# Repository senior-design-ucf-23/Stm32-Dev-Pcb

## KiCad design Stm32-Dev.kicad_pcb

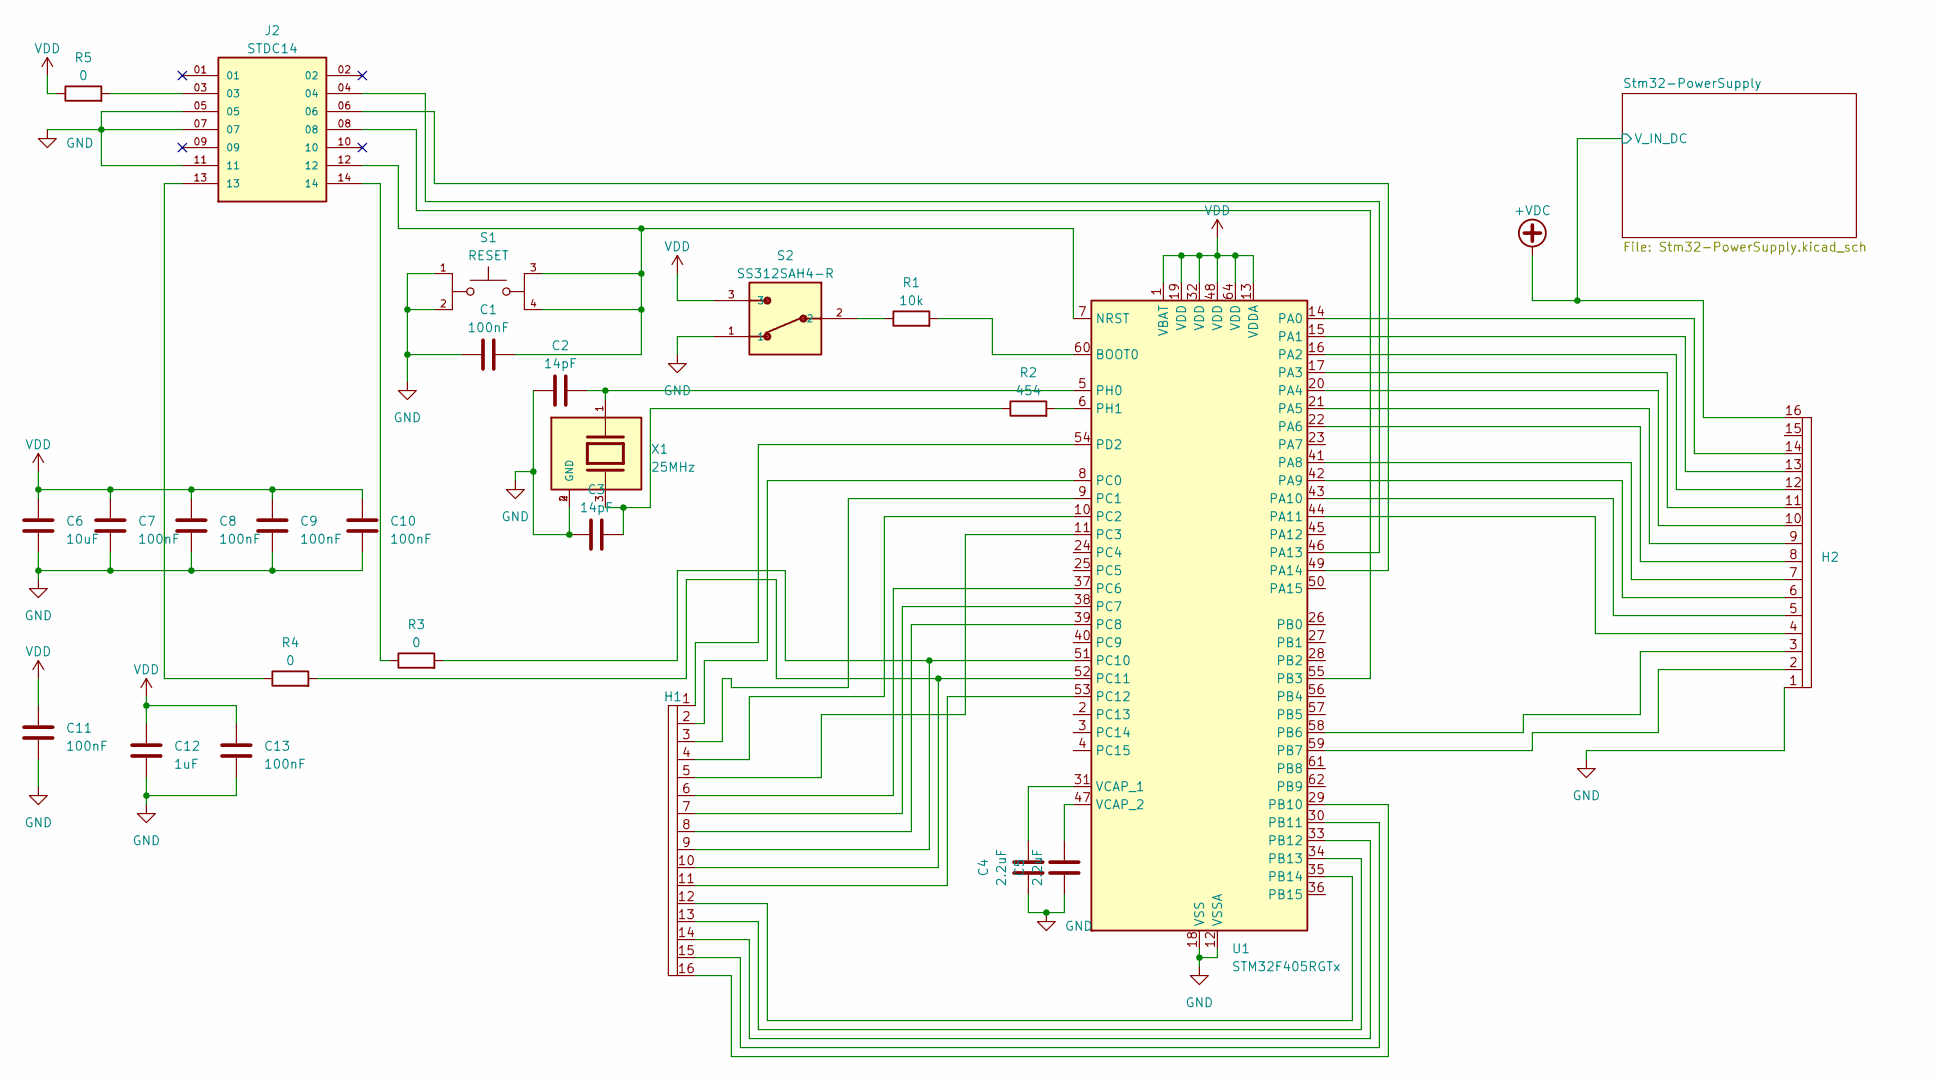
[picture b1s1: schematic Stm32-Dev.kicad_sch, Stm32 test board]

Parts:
C1, C7, C8, C9, C10, C11, C13: 100nF; C_0805_2012Metric
C2, C3: 14pF; C_0805_2012Metric
C4, C5: 2.2uF; C_0805_2012Metric
C6: 10uF; C_0805_2012Metric
C12: 1uF; C_0805_2012Metric
H1, H2: HDRV16
J2: STDC14; SAMTEC_FTSH-107-01-L-DV-K; PARTREV R
R1: 10k; R_0805_2012Metric
R2: 454; R_0805_2012Metric
R3, R4, R5: 0; R_0805_2012Metric
S1: RESET; SW_TL3301AF160QG; PARTREV E
S2: SS312SAH4-R; SW_SS312SAH4-R
U1: STM32F405RGTx; LQFP-64_10x10mm_P0.5mm
X1: 25MHz; XTAL_ABM10W-25.0000MHZ-7-D1X-T3; PARTREV 10.06.2020

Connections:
+VDC: H2.16; also elsewhere on the board
GND: C1.2, C2.2, C3.2, C4.2, C5.2, C6.2, C7.2, C8.2, C9.2, C10.2, C11.2, C12.2, C13.2, H2.1, J2.05, J2.07, J2.11, S1.1, S1.2, S2.1, U1.12 (VSSA), U1.18 (VSS), U1.63 (VSS), X1.2 (GND), X1.4 (GND); also elsewhere on the board
unnamed: C3.1, R2.1, X1.3
unnamed: J2.03, R5.2
unnamed: J2.13, R4.1
unnamed: J2.14, R3.1
unnamed: R1.1, S2.2
unnamed: R1.2, U1.60 (BOOT0)
unnamed: C1.1, J2.12, S1.3, S1.4, U1.7 (NRST)
unnamed: H2.14, U1.14 (PA0)
unnamed: H2.13, U1.15 (PA1)
unnamed: H2.12, U1.16 (PA2)
unnamed: H2.11, U1.17 (PA3)
unnamed: H2.10, U1.20 (PA4)
unnamed: H2.9, U1.21 (PA5)
unnamed: H2.8, U1.22 (PA6)
unnamed: H2.7, U1.41 (PA8)
unnamed: H2.6, U1.42 (PA9)
unnamed: H2.5, U1.43 (PA10)
unnamed: H2.4, U1.44 (PA11)
unnamed: J2.04, U1.46 (PA13)
unnamed: J2.06, U1.49 (PA14)
unnamed: J2.08, U1.55 (PB3)
unnamed: H2.3, U1.58 (PB6)
unnamed: H2.2, U1.59 (PB7)
unnamed: H1.16, U1.29 (PB10)
unnamed: H1.15, U1.30 (PB11)
unnamed: H1.14, U1.33 (PB12)
unnamed: H1.13, U1.34 (PB13)
unnamed: H1.12, U1.35 (PB14)
unnamed: H1.2, U1.8 (PC0)
unnamed: H1.3, U1.9 (PC1)
unnamed: H1.4, U1.10 (PC2)
unnamed: H1.5, U1.11 (PC3)
unnamed: H1.6, U1.37 (PC6)
unnamed: H1.7, U1.38 (PC7)
unnamed: H1.8, U1.39 (PC8)
unnamed: H1.9, R3.2, U1.51 (PC10)
unnamed: H1.10, R4.2, U1.52 (PC11)
unnamed: H1.11, U1.53 (PC12)
unnamed: H1.1, U1.54 (PD2)
unnamed: C2.1, U1.5 (PH0), X1.1
unnamed: R2.2, U1.6 (PH1)
unnamed: C4.1, U1.31 (VCAP_1)
unnamed: C5.1, U1.47 (VCAP_2)
VDD: C6.1, C7.1, C8.1, C9.1, C10.1, C11.1, C12.1, C13.1, R5.1, S2.3, U1.1 (VBAT), U1.13 (VDDA), U1.19 (VDD), U1.32 (VDD), U1.48 (VDD), U1.64 (VDD); also elsewhere on the board

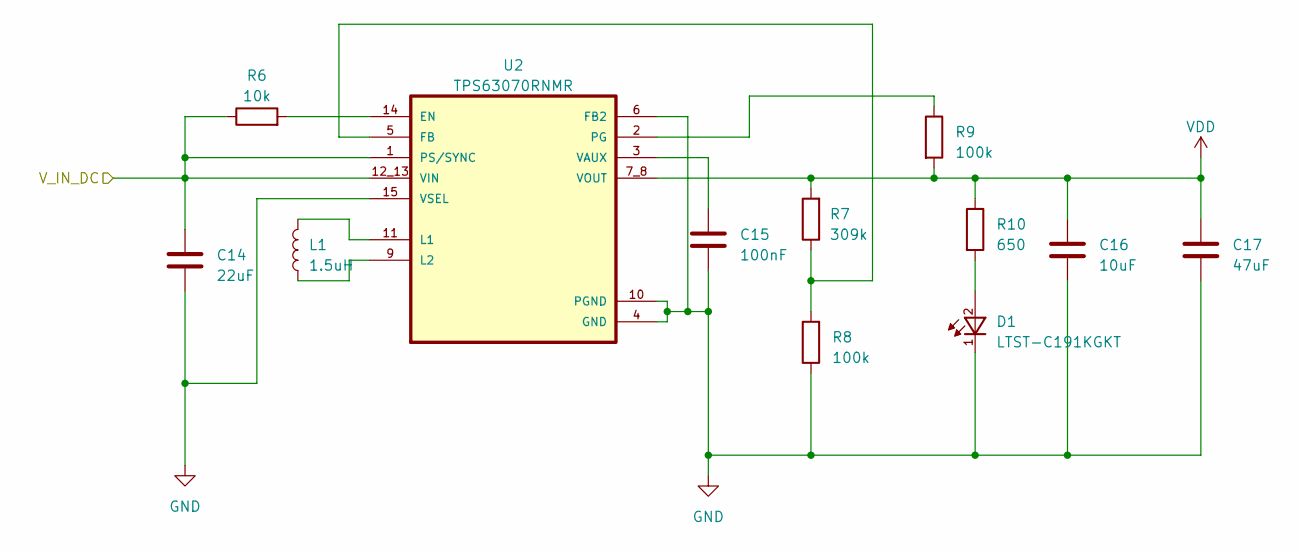
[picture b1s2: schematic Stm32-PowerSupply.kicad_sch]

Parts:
C14: 22uF; C_0805_2012Metric
C15: 100nF; C_0805_2012Metric
C16: 10uF; C_0805_2012Metric
C17: 47uF; C_0805_2012Metric
D1: LTST-C191KGKT; 0603
L1: 1.5uH; L_Bourns_SRN8040TA
R6: 10k; R_0805_2012Metric
R7: 309k; R_0805_2012Metric
R8, R9: 100k; R_0805_2012Metric
R10: 650; R_0805_2012Metric
U2: TPS63070RNMR; VREG_TPS63070RNMR

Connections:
+VDC: C14.1, R6.1, U2.1 (PS/SYNC), U2.12_13 (VIN); also elsewhere on the board
GND: C14.2, C15.2, C16.2, C17.2, D1.1, R8.1, U2.4 (GND), U2.6 (FB2), U2.10 (PGND), U2.15 (VSEL); also elsewhere on the board
unnamed: D1.2, R10.2
unnamed: R6.2, U2.14 (EN)
unnamed: R7.1, R8.2, U2.5 (FB)
unnamed: L1.2, U2.11 (L1)
unnamed: L1.1, U2.9 (L2)
unnamed: R9.1, U2.2 (PG)
unnamed: C15.1, U2.3 (VAUX)
VDD: C16.1, C17.1, R7.2, R9.2, R10.1, U2.7_8 (VOUT); also elsewhere on the board

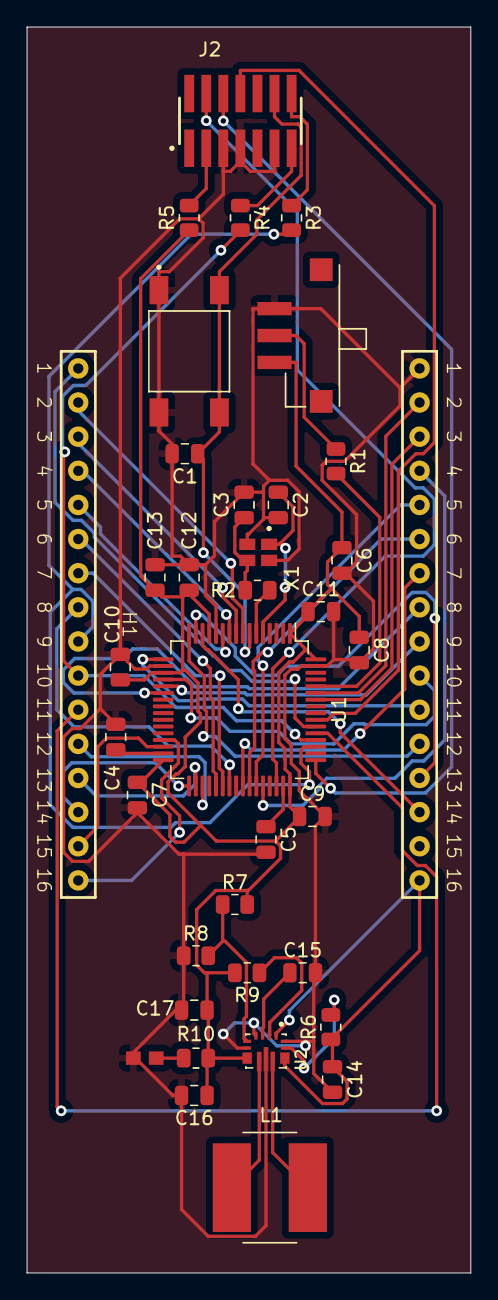
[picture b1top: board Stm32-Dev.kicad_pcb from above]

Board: 2 copper layers, 33.0 x 92.7 mm, 37 parts (0 on the bottom side), 53 nets.

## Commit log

2023-06-16 Initial MCU
2023-06-17 Basic MCU Setup
2023-06-19 PCB start
2023-06-20 PCB ready for routing
2023-06-20 Changed Boot Switch
2023-06-20 Used Libraries
2023-07-03 First Test Board

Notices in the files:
Stm32-Dev.kicad_sch:
creativecommons.org/licenses/by/4.0
License: CC BY 4.0
